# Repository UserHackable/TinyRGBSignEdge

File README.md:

## TinyRGBSignEdge 

### Board dimensions

* (290000, 90000) original units
* (2.9000, 0.9000) inches
* (73.6600, 22.8600) mm

| Front | Back |
| --- | --- |
|  |  |

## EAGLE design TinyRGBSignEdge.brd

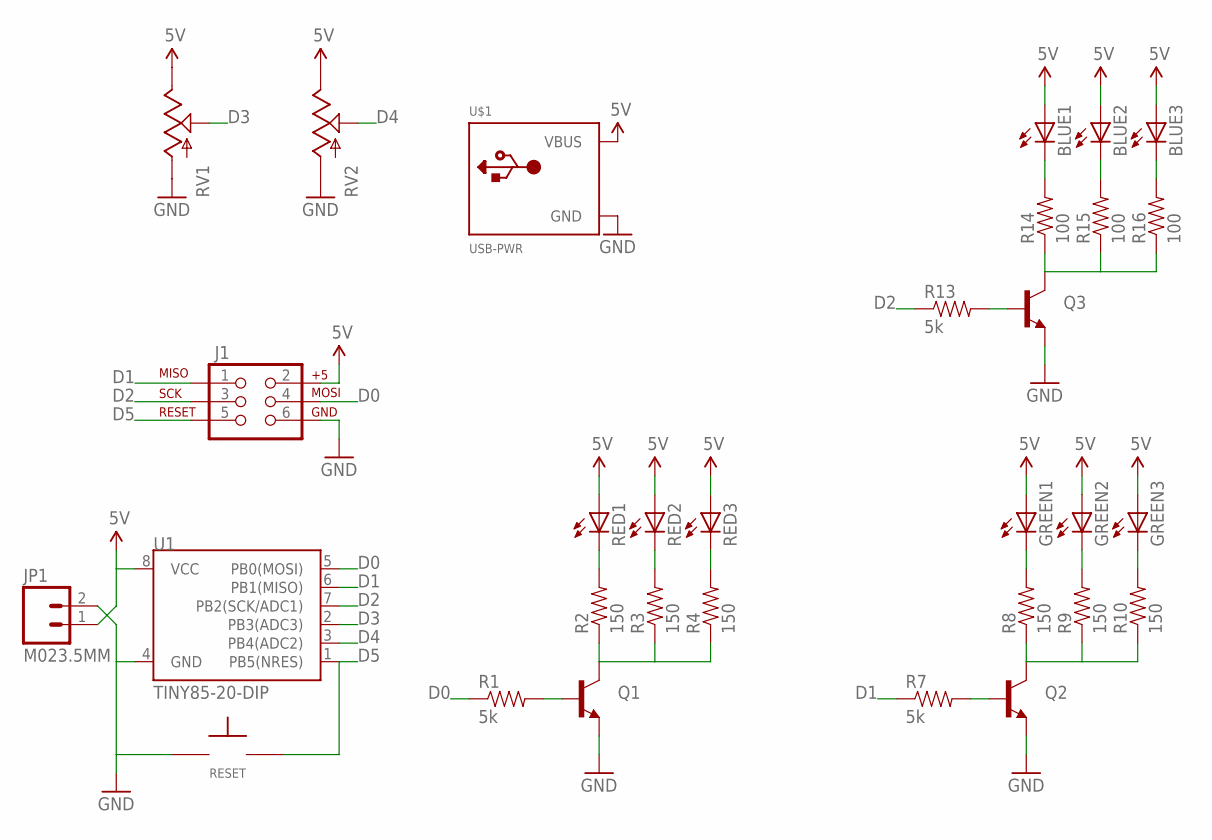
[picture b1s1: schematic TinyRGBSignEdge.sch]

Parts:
BLUE1, BLUE2, BLUE3: LED5MM
GREEN1, GREEN2, GREEN3: LED5MM
J1: AVR_SPI_PRG_6PTH; 2X3
JP1: M023.5MM; SCREWTERMINAL-3.5MM-2
Q1, Q2, Q3: TRANSISTOR_NPNTO-92-AMMO; TO-92-AMMO
R1, R7, R13: 5k; AXIAL-0.3
R2, R3, R4, R8, R9, R10: 150; AXIAL-0.3
R14, R15, R16: 100; AXIAL-0.3
RED1, RED2, RED3: LED5MM
RESET: TAC_SPST_NO
RV1, RV2: POTTRIM; TRIM_POT
U1: TINY85-20-DIP; DIP08
U$1: USB-PWR; USB-MINIB-THM-MOLEX-PWRONLY

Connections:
5V: BLUE1.A, BLUE2.A, BLUE3.A, GREEN1.A, GREEN2.A, GREEN3.A, J1.2, JP1.1, RED1.A, RED2.A, RED3.A, RV1.2 (E), RV2.2 (E), U1.8 (VCC), U$1.VBUS
BLUE2: BLUE2.K (C), R15.P$2 (2)
D0: J1.4, R1.P$1 (1), U1.5 (PB0(MOSI))
D1: J1.1, R7.P$1 (1), U1.6 (PB1(MISO))
D2: J1.3, R13.P$1 (1), U1.7 (PB2(SCK/ADC1))
D3: RV1.1 (S), U1.2 (PB3(ADC3))
D4: RV2.1 (S), U1.3 (PB4(ADC2))
D5: J1.5, RESET.P$2, U1.1 (PB5(NRES))
GND: J1.6, JP1.2, Q1.1 (E), Q2.1 (E), Q3.1 (E), RESET.P$1, RV1.3 (A), RV2.3 (A), U1.4 (GND), U$1.GND
GREEN1: GREEN1.K (C), R8.P$2 (2)
unnamed: Q1.2 (B), R1.P$2 (2)
unnamed: R2.P$2 (2), RED1.K (C)
unnamed: R3.P$2 (2), RED2.K (C)
unnamed: Q1.3 (C), R2.P$1 (1), R3.P$1 (1), R4.P$1 (1)
unnamed: Q2.2 (B), R7.P$2 (2)
unnamed: GREEN2.K (C), R9.P$2 (2)
unnamed: GREEN3.K (C), R10.P$2 (2)
unnamed: Q2.3 (C), R8.P$1 (1), R9.P$1 (1), R10.P$1 (1)
unnamed: Q3.2 (B), R13.P$2 (2)
unnamed: BLUE1.K (C), R14.P$2 (2)
unnamed: BLUE3.K (C), R16.P$2 (2)
unnamed: Q3.3 (C), R14.P$1 (1), R15.P$1 (1), R16.P$1 (1)
RED3: R4.P$2 (2), RED3.K (C)

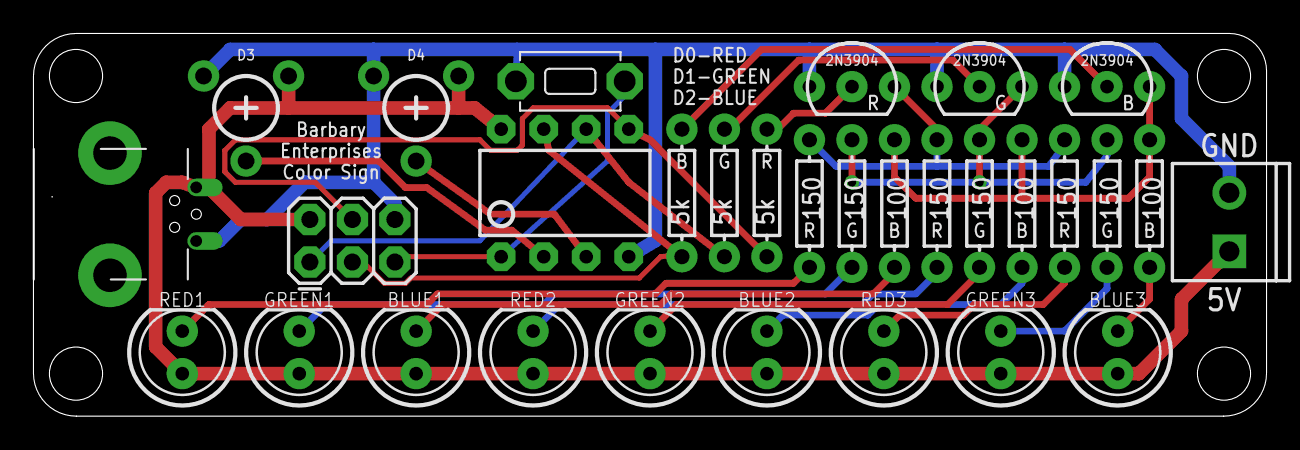
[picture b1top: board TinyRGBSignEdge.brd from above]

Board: 2 copper layers, 73.7 x 22.9 mm, 31 parts (0 on the bottom side), 23 nets.

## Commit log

2016-04-08 from Makefile

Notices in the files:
parts and their libraries:
SparkFun-DigitalIC: Licensing: Creative Commons ShareAlike 4.0 International - https://creativecommons.org/licenses/by-sa/4.0
